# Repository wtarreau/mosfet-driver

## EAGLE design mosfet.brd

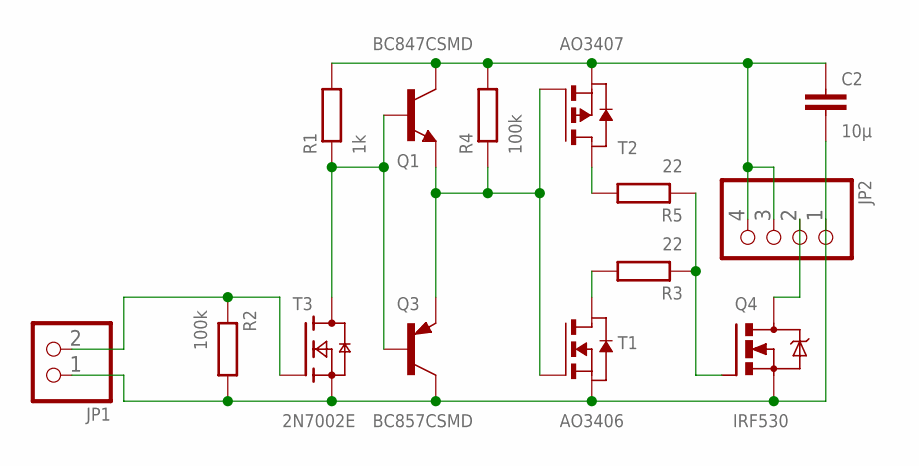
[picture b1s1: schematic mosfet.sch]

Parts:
C2: 10µ; C0805K
JP1: PINHD-1X2; 1X02
JP2: PINHD-1X4; 1X04
Q1: BC847CSMD; SOT23
Q3: BC857CSMD; SOT23-BEC
Q4: IRF530; TO220BV
R1: 1k; R0805
R2, R4: 100k; R0805
R3, R5: 22; R0805
T1: AO3406; SOT-23
T2: AO3407; SOT-23
T3: 2N7002E; SOT23

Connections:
unnamed: Q4.G, R3.1, R5.1
unnamed: R5.2, T2.1 (D)
unnamed: C2.2, JP1.1, JP2.1, Q3.C, Q4.S, R2.2, T1.2 (S), T3.2 (S)
unnamed: JP1.2, R2.1, T3.1 (G)
unnamed: Q1.1 (B), Q3.B, R1.1, T3.3 (D)
unnamed: Q1.2 (E), Q3.E, R4.1, T1.3 (G), T2.3 (G)
unnamed: C2.1, JP2.3, JP2.4, Q1.3 (C), R1.2, R4.2, T2.2 (S)
unnamed: R3.2, T1.1 (D)
unnamed: JP2.2, Q4.D

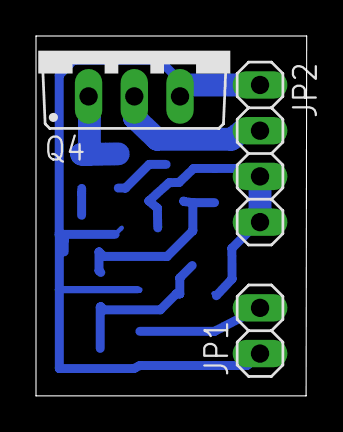
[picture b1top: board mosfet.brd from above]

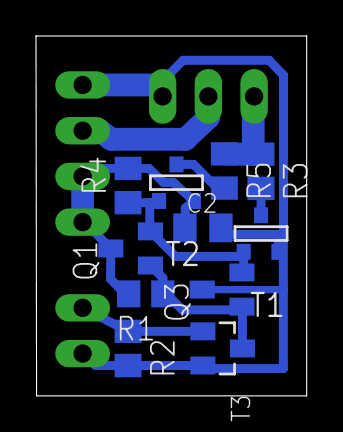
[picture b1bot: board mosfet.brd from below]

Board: 2 copper layers, 15.0 x 20.0 mm, 14 parts (11 on the bottom side), 9 nets.

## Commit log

2020-08-17 Update mosfet driver to v1
2020-08-17 Update mosfet driver to v2
2020-08-17 Update mosfet driver to v3
2020-08-17 Update mosfet driver to v4
2020-08-17 Update mosfet driver to v5
2020-08-17 output: provide the png & pdf outputs
    These are easier to exploit.
